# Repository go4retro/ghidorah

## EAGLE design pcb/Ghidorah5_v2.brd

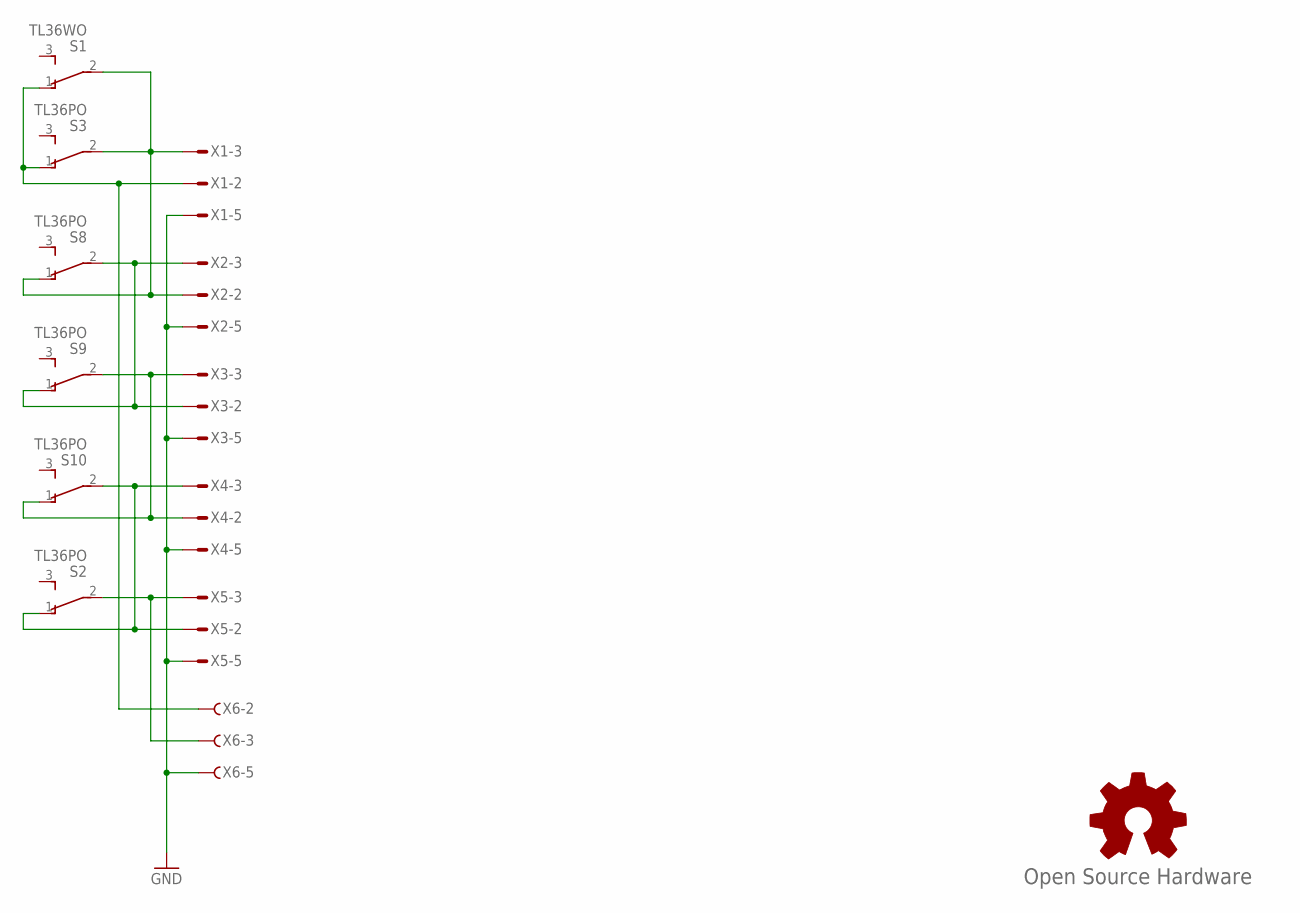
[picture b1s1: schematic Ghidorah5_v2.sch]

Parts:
GOLD_ORB_SM1: Open Source Hardware; OSHW_5MM
S1: TL36WO; TL3XWO
S2, S3, S8, S9, S10: TL36PO; TL3XPO
X1: M09DS; M09D
X2, X3, X4, X5: M09VS; M09V
X6: F09DS; F09D

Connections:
2M: S1.1 (O), S3.1 (O), X1.2, X6.2
3F: S2.2, X5.3, X6.3
GND: X1.5, X2.5, X3.5, X4.5, X5.5, X6.5
unnamed: S1.2, S3.2, S8.1 (O), X1.3, X2.2
unnamed: S8.2, S9.1 (O), X2.3, X3.2
unnamed: S9.2, S10.1 (O), X3.3, X4.2
unnamed: S2.1 (O), S10.2, X4.3, X5.2

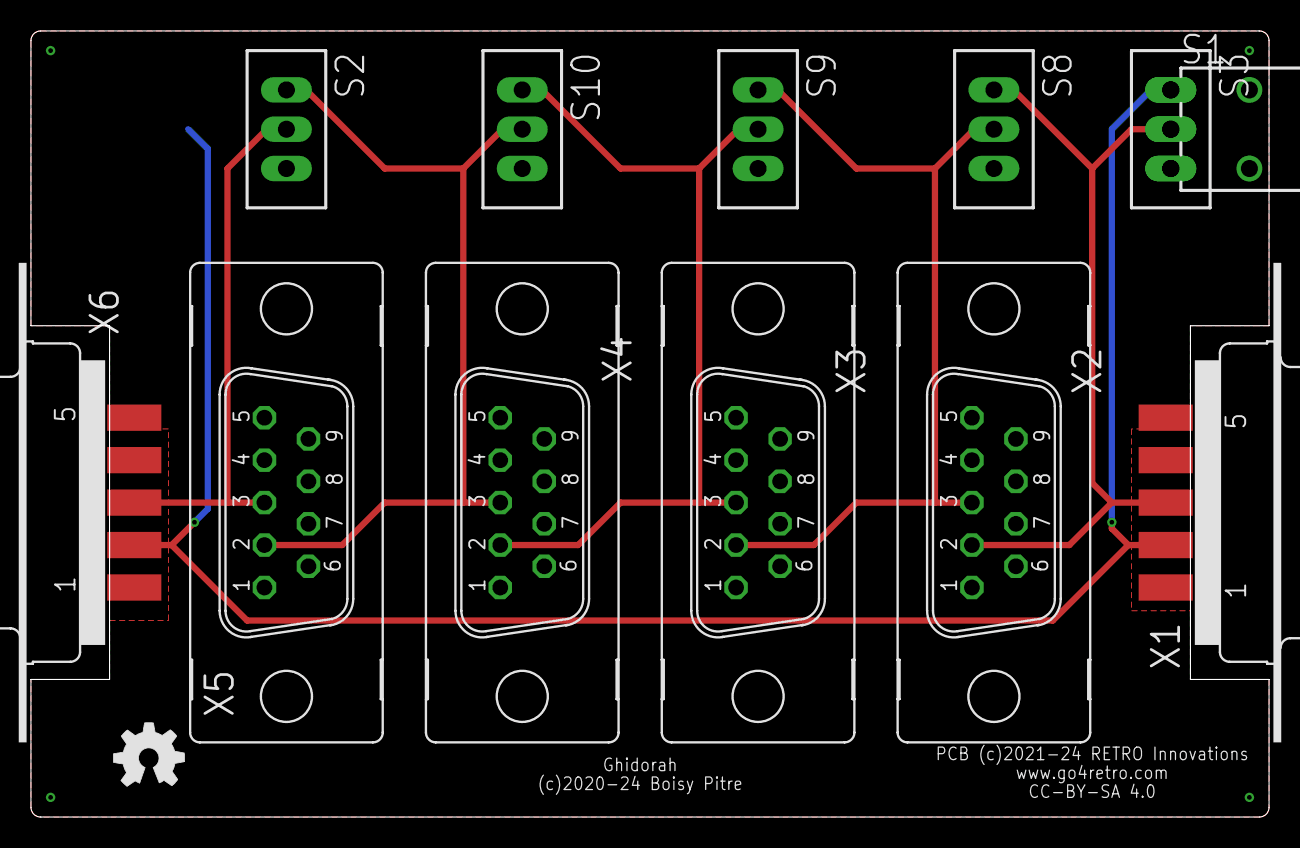
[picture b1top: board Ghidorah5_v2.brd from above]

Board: 2 copper layers, 80.0 x 50.8 mm, 13 parts (0 on the bottom side), 7 nets.

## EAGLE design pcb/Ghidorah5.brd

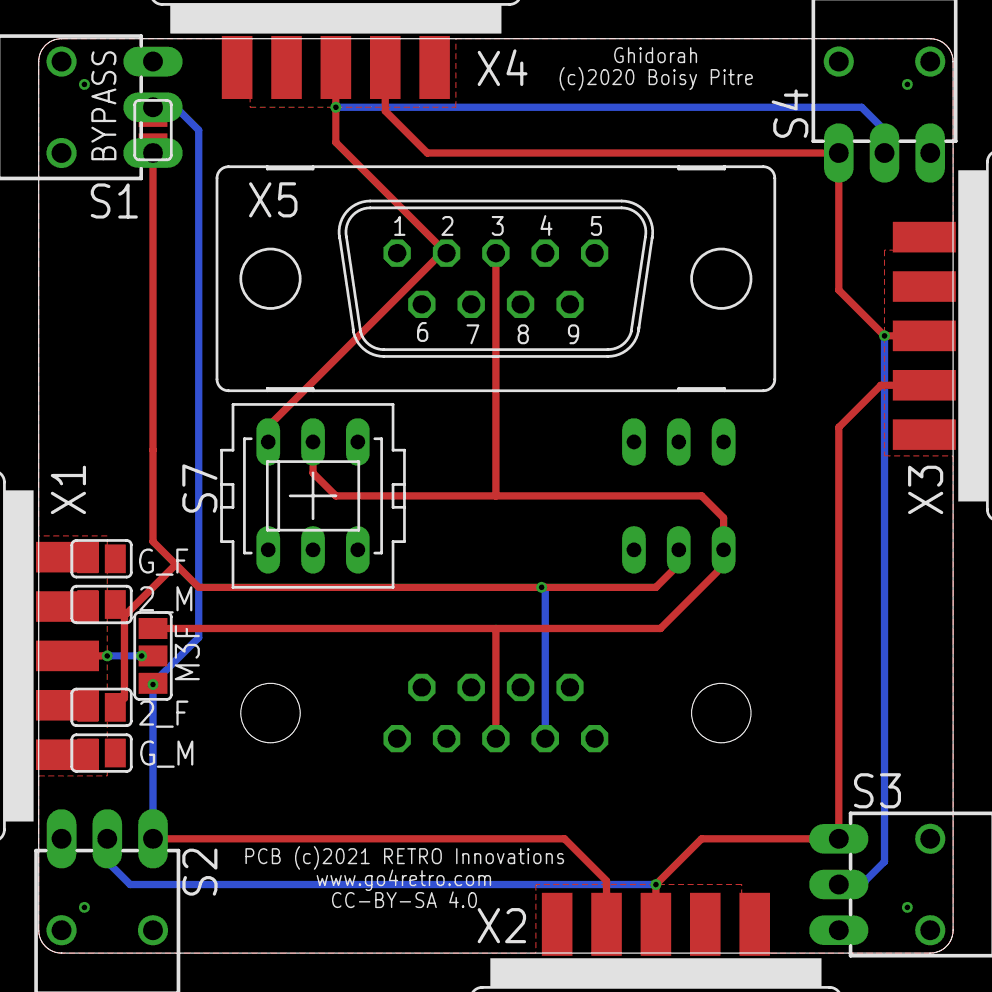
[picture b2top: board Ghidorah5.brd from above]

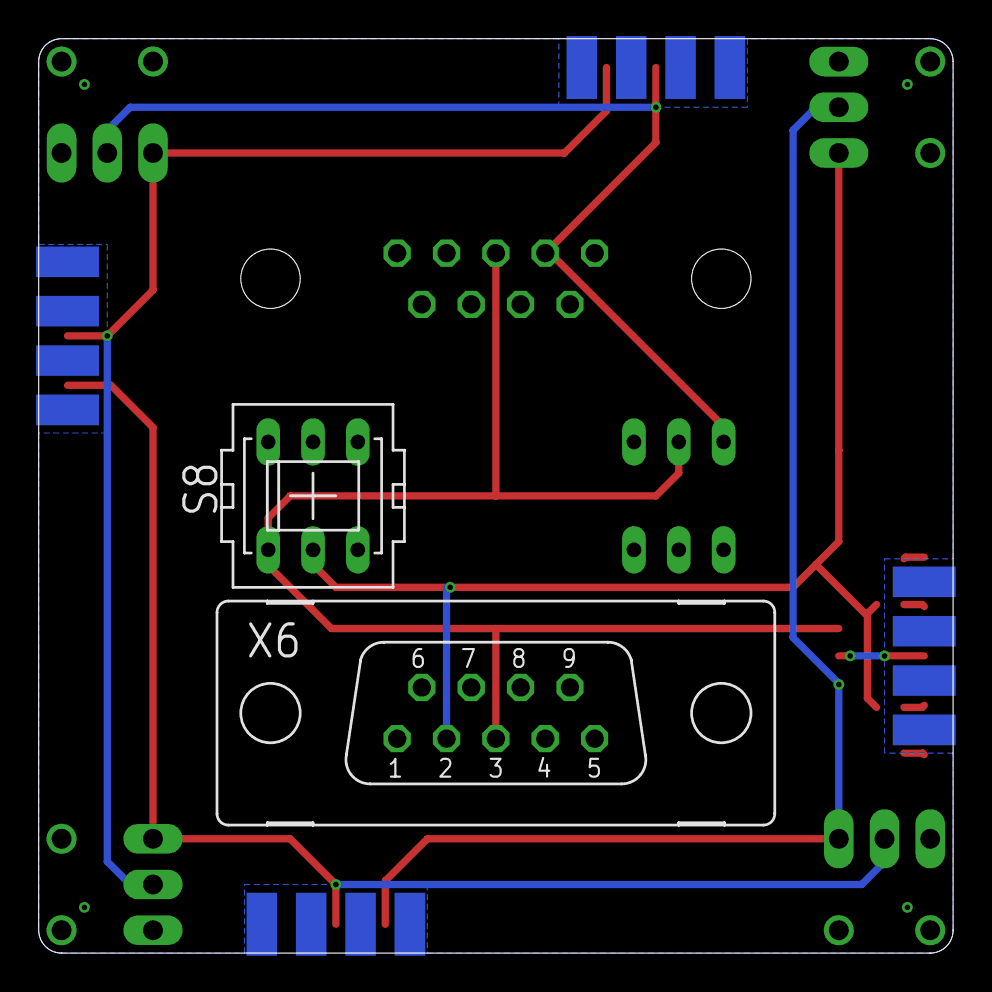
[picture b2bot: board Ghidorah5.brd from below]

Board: 2 copper layers, 50.8 x 50.8 mm, 18 parts (2 on the bottom side), 12 nets.

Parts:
2_F, 2_M: SJ
BYPASS: SJ
G_F: SJ
G_M: SJ
M3F: SJ_2
S1, S2, S3, S4: TL36WO; TL3XWO
S7, S8: PVA2R
X1, X2, X3, X4: M09D
X5: M09V
X6: F09V

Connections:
1_2: 2_F.1, 2_M.1, BYPASS.1, S1.1, S8.5, X6.2
2F: 2_F.2, X1.4
2M: 2_M.2, X1.2
3: M3F.2, X1.3
3F: M3F.1, S7.2, S8.6, X5.3, X6.3
3M: BYPASS.2, M3F.3, S1.2, S2.1, X2.2
GND: G_F.1, G_M.1, X2.5, X3.5, X4.5, X5.5, X6.5
GNDF: G_F.2, X1.1
GNDM: G_M.2, X1.5
unnamed: S2.2, S3.1, X2.3, X3.2
unnamed: S3.2, S4.1, X3.3, X4.2
unnamed: S4.2, S7.3, X4.3, X5.2

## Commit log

2024-05-05 New design
2024-05-05 Added pics

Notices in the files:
pcb/Ghidorah5.brd:
PCB (c)2021 RETRO Innovations
CC-BY-SA 4.0
(c)2020 Boisy Pitre
pcb/Ghidorah5_v2.brd:
PCB (c)2021-24 RETRO Innovations
(c)2020-24 Boisy Pitre
parts and their libraries:
SparkFun: Licensing: CC v3.0 Share-Alike You are welcome to use this library for commercial purposes.
